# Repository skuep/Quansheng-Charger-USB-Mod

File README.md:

# Quansheng Charger Modification for USB Type-C Input
This is a mod for the original Quansheng (UV-K5) charging cradle so you can charge your radio using via USB--C

# Order at JLCPCB
Use the production files in the kicad folder to directly order at JLCPCB.

- Upload [GERBER-quansheng-usb-charger.zip](kicad/quansheng-usb-charger/jlcpcb/production_files/GERBER-quansheng-usb-charger.zip?raw=true) to JLCPCB.
- Choose 1.6mm PCB thickness, LeadFree HASL
- Enable "PCB Assembly" with "Economic" type. Select "Tooling Holes Added by Customer"
- Press NEXT button
- Upload [BOM-quansheng-usb-charger.csv](kicad/quansheng-usb-charger/jlcpcb/production_files/BOM-quansheng-usb-charger.csv?raw=true) and [CPL-quansheng-usb-charger.csv](kicad/quansheng-usb-charger/jlcpcb/production_files/CPL-quansheng-usb-charger.csv?raw=true) files. 
- Press Continue for the Error message of some missing parts (It's okay). 
- **Make sure all parts are selected for placement** and Press Next
- Check Placement and Press Next
- Select Production Description (e.g. Smart Products and Accessories -> Charger)
- Save To Cart 

# Assemble
1. Buy a new Quansheng UV-K5 charging cradle from AliExpress, if you want to keep your current one

2. Open up charging cradle

3. Remove the original PCB, slightly push one of the hooks to the side with your finger for easier release

4. Desolder the two large spring contacts (3 solder joints each) and the 3-Pin LED at the bottom e.g. using desoldering wick.

5. Get the freshly made Mod PCBs from JLCPCB

6. Solder in the spring contacts from one of the previous steps

7. Insert the blind-plug in the upper shell half. Either use the 3D printed one (see ``Blind-Plug.stl``) or modify the original one by cutting it.

8. Feed in the spring contacts into their seating. Push down at the USB-C connector side until it is seated

9. Next, also push in the opposite side. Note that you might need to use a flathead screw-driver to help push the hook to the side a bit while pressing down.

10. Lastly, put the LED in place and re-solder it.

11. Done! Test it and put the screws back in

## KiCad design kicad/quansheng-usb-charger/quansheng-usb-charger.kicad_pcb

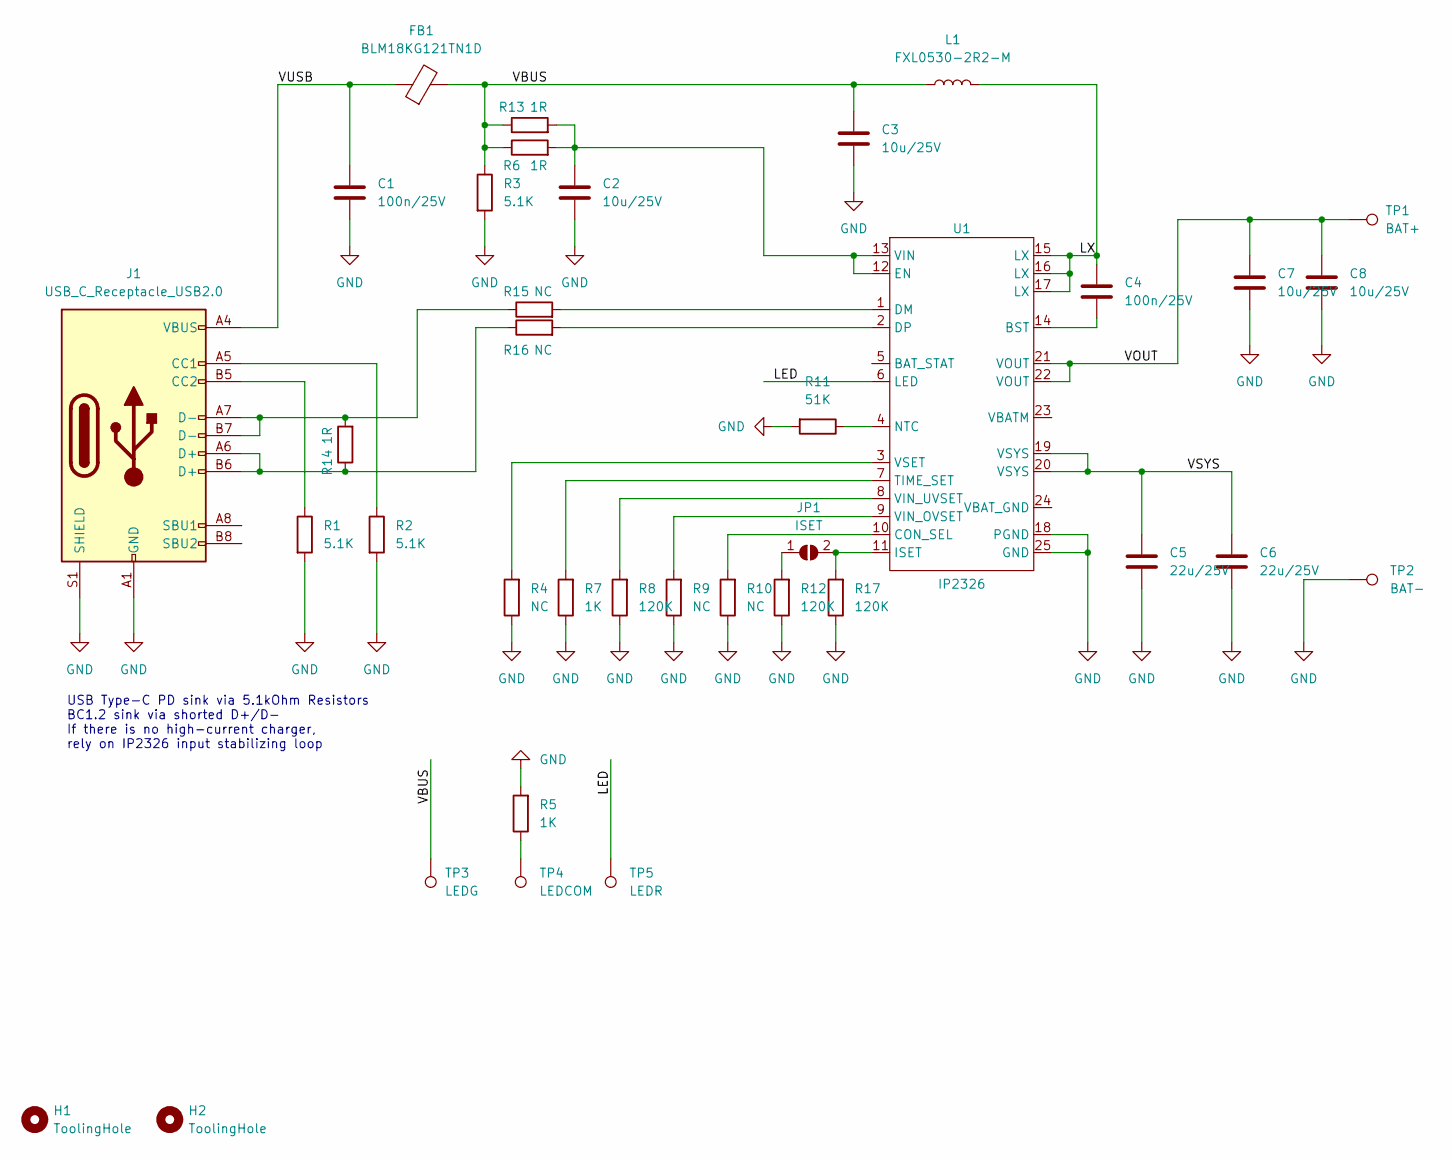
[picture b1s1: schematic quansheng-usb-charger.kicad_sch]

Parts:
C1, C4: 100n/25V; C_0603_1608Metric; LCSC C14663
C2, C3, C7, C8: 10u/25V; C_0805_2012Metric; LCSC C15850
C5, C6: 22u/25V; C_0805_2012Metric; LCSC C45783
FB1: BLM18KG121TN1D; L_0603_1608Metric; LCSC C85831
H1, H2: ToolingHole; TOOLING-HOLE
J1: USB_C_Receptacle_USB2.0; USB_C_Receptacle_GCT_USB4105-xx-A_16P_TopMnt_Horizontal; LCSC C2988369
JP1: ISET; SolderJumper-2_P1.3mm_Open_TrianglePad1.0x1.5mm
L1: FXL0530-2R2-M; L_Sunlord_MWSA0518_5.4x5.2mm; LCSC C177247
R1, R2, R3: 5.1K; R_0603_1608Metric; LCSC C23186
R4, R9, R10, R15, R16: NC; R_0603_1608Metric
R5, R7: 1K; R_0603_1608Metric; LCSC C21190
R6, R13, R14: 1R; R_0603_1608Metric; LCSC C22936
R8, R12, R17: 120K; R_0603_1608Metric; LCSC C25808
R11: 51K; R_0603_1608Metric; LCSC C23196
TP1: BAT+; SPRING-CONTACT
TP2: BAT-; SPRING-CONTACT
TP3: LEDG; TestPoint_THTPad_2.0x2.0mm_Drill1.0mm
TP4: LEDCOM; TestPoint_THTPad_2.0x2.0mm_Drill1.0mm
TP5: LEDR; TestPoint_THTPad_2.0x2.0mm_Drill1.0mm
U1: IP2326; HVQFN-24-1EP_4x4mm_P0.5mm_EP2.5x2.5mm; LCSC C2832094

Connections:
/LED: TP5.1, U1.6 (LED)
/LX: C4.2, L1.2, U1.15 (LX), U1.16 (LX), U1.17 (LX)
/VBUS: C3.1, FB1.2, L1.1, R3.1, R6.1, R13.1, TP3.1
/VOUT: C7.1, C8.1, TP1.1, U1.21 (VOUT), U1.22 (VOUT)
/VSYS: C5.1, C6.1, U1.19 (VSYS), U1.20 (VSYS)
/VUSB: C1.2, FB1.1, J1.A4 (VBUS), J1.A9 (VBUS), J1.B4 (VBUS), J1.B9 (VBUS)
GND: C1.1, C2.2, C3.2, C5.2, C6.2, C7.2, C8.2, J1.A1 (GND), J1.A12 (GND), J1.B1 (GND), J1.B12 (GND), J1.S1 (SHIELD), R1.2, R2.2, R3.2, R4.1, R5.2, R7.1, R8.1, R9.1, R10.1, R11.2, R12.1, R17.1, TP2.1, U1.18 (PGND), U1.25 (GND)
unnamed: C2.1, R6.2, R13.2, U1.12 (EN), U1.13 (VIN)
unnamed: C4.1, U1.14 (BST)
unnamed: J1.A5 (CC1), R2.1
unnamed: J1.A6 (D+), J1.B6 (D+), R14.1, R16.1
unnamed: J1.A7 (D-), J1.B7 (D-), R14.2, R15.1
unnamed: J1.B5 (CC2), R1.1
unnamed: R4.2, U1.3 (VSET)
unnamed: R5.1, TP4.1
unnamed: R7.2, U1.7 (TIME_SET)
unnamed: R8.2, U1.8 (VIN_UVSET)
unnamed: R9.2, U1.9 (VIN_OVSET)
unnamed: R10.2, U1.10 (CON_SEL)
unnamed: R11.1, U1.4 (NTC)
unnamed: JP1.1 (A), R12.2
unnamed: R15.2, U1.1 (DM)
unnamed: R16.2, U1.2 (DP)
unnamed: JP1.2 (B), R17.2, U1.11 (ISET)

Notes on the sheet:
USB Type-C PD sink via 5.1kOhm Resistors BC1.2 sink via shorted D+/D- If there is no high-current charger, rely on IP2326 input stabilizing loop

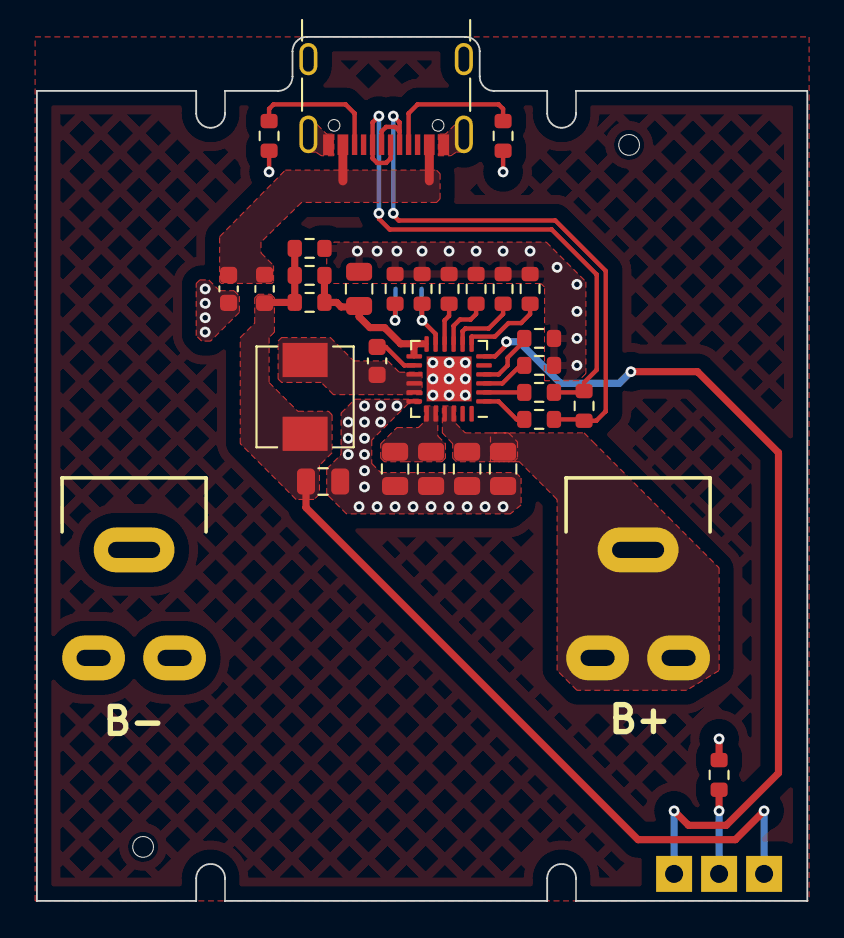
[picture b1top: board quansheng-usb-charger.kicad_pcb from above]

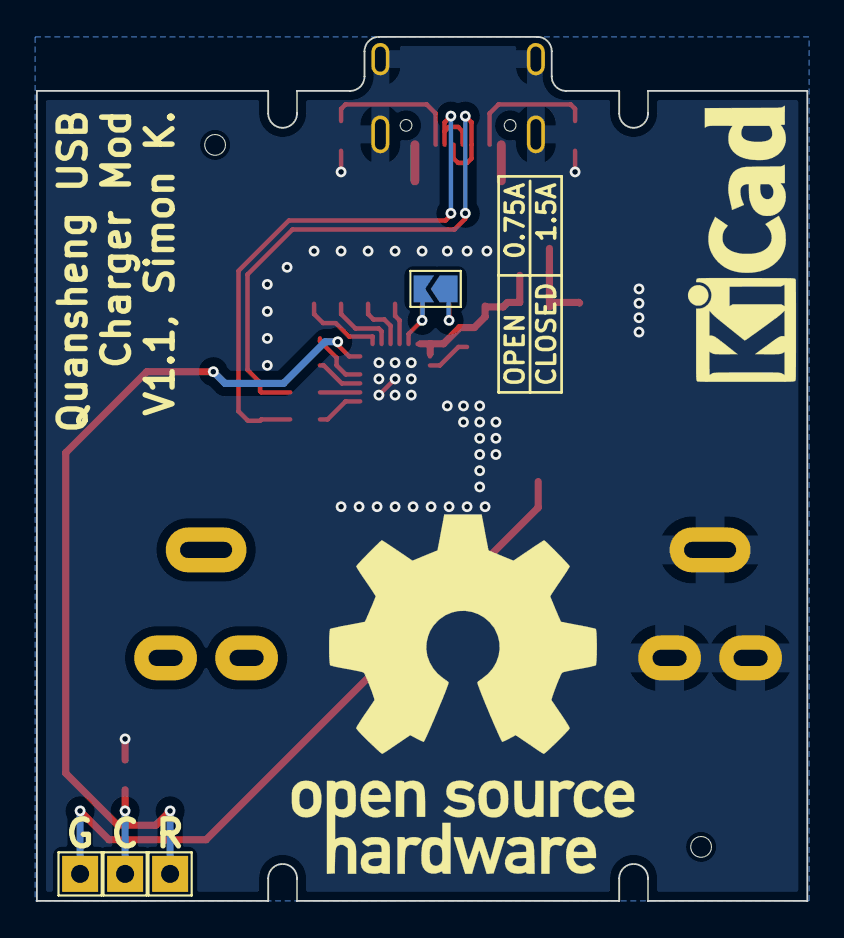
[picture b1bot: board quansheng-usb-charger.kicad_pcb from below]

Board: 2 copper layers, 42.8 x 48.0 mm, 37 parts (4 on the bottom side), 24 nets.

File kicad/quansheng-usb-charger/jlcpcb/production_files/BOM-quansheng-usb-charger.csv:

Comment,Designator,Footprint,LCSC
100n/25V,"C1,C4",C_0603_1608Metric,C14663
10u/25V,"C2,C3,C7,C8",C_0805_2012Metric,C15850
FXL0530-2R2-M,L1,L_Sunlord_MWSA0518_5.4x5.2mm,C177247
1K,"R5,R7",R_0603_1608Metric,C21190
1R,"R13,R14,R6",R_0603_1608Metric,C22936
5.1K,"R1,R2,R3",R_0603_1608Metric,C23186
51K,R11,R_0603_1608Metric,C23196
120K,"R12,R17,R8",R_0603_1608Metric,C25808
IP2326,U1,HVQFN-24-1EP_4x4mm_P0.5mm_EP2.5x2.5mm,C2832094
USB_C_Receptacle_USB2.0,J1,USB_C_Receptacle_GCT_USB4105-xx-A_16P_TopMnt_Horizontal,C2988369
22u/25V,"C5,C6",C_0805_2012Metric,C45783
BLM18KG121TN1D,FB1,L_0603_1608Metric,C85831
NC,R4,R_0603_1608Metric,
BAT-,TP2,SPRING-CONTACT,
NC,R9,R_0603_1608Metric,
BAT+,TP1,SPRING-CONTACT,
NC,R10,R_0603_1608Metric,
LEDG,TP3,TestPoint_THTPad_2.0x2.0mm_Drill1.0mm,
LEDCOM,TP4,TestPoint_THTPad_2.0x2.0mm_Drill1.0mm,
LEDR,TP5,TestPoint_THTPad_2.0x2.0mm_Drill1.0mm,
ToolingHole,H2,TOOLING-HOLE,
ToolingHole,H1,TOOLING-HOLE,
NC,R16,R_0603_1608Metric,
NC,R15,R_0603_1608Metric,
ISET,JP1,SolderJumper-2_P1.3mm_Open_TrianglePad1.0x1.5mm,

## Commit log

2025-10-12 Add JLCPCB files and README
2025-10-12 Improve mechanical fit
2025-10-12 Silkscreen adjustments
2025-10-12 Add Tooling Holes
2025-10-25 Don't use the built-in USB AFC standard
2025-10-25 Add jumper pad for optional 1.5A charging current
2025-10-25 Add instructional photos
2025-10-25 Add 3D printed blind plug for back
2025-10-25 Update README.md
    Add instructions
2025-10-25 Update README.md
    Improve JLCPCB instructions
